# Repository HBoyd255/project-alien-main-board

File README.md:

# Project A.L.I.E.N. Main Board

<!-- Harry Boyd - hboyd255@gmail.com - 22/07/2024 -->

This is the repository for the main board of Project A.L.I.E.N. (Autonomous
Labyrinth Investigator, Explorer, Navigator).

This project started as a University project for the module
[Robotics Design and Construction](https://www.york.ac.uk/students/studying/manage/programmes/module-catalogue/module/ELE00098H).
To get us started, the University provided us with a main board, called the ARB
(Arduino Robotics Board), which was designed to break out the pins of an Arduino
Nano 33 BLE into connectors that were easier to use. However, when the module
concluded, the University wanted the boards back, so I designed my own.

## Testing

The code to test the board has been split into separate repositories.

- [Motors and Encoders](https://github.com/HBoyd255/project-alien-motor-test-code)
- [Bumper and NES Shift Registers](https://github.com/HBoyd255/project-alien-shift-register-test-code)
- [LED Strip and Level Shifter](https://github.com/HBoyd255/project-alien-led-strip-test-code)
- [Ultrasonic Sensor](https://github.com/HBoyd255/project-alien-ultrasonic-test-code)
- [Infrared Sensors and I2C Multiplexer](https://github.com/HBoyd255/project-alien-infrared-test-code)

## Expansion Boards

The Project A.L.I.E.N. Main Board has been designed to to take expansion boards.
This utilises the 3 left-over GPIO pins, D11, D12 and D13.

- [Extra buttons ](https://github.com/HBoyd255/project-alien-expansion-demo-buttons)

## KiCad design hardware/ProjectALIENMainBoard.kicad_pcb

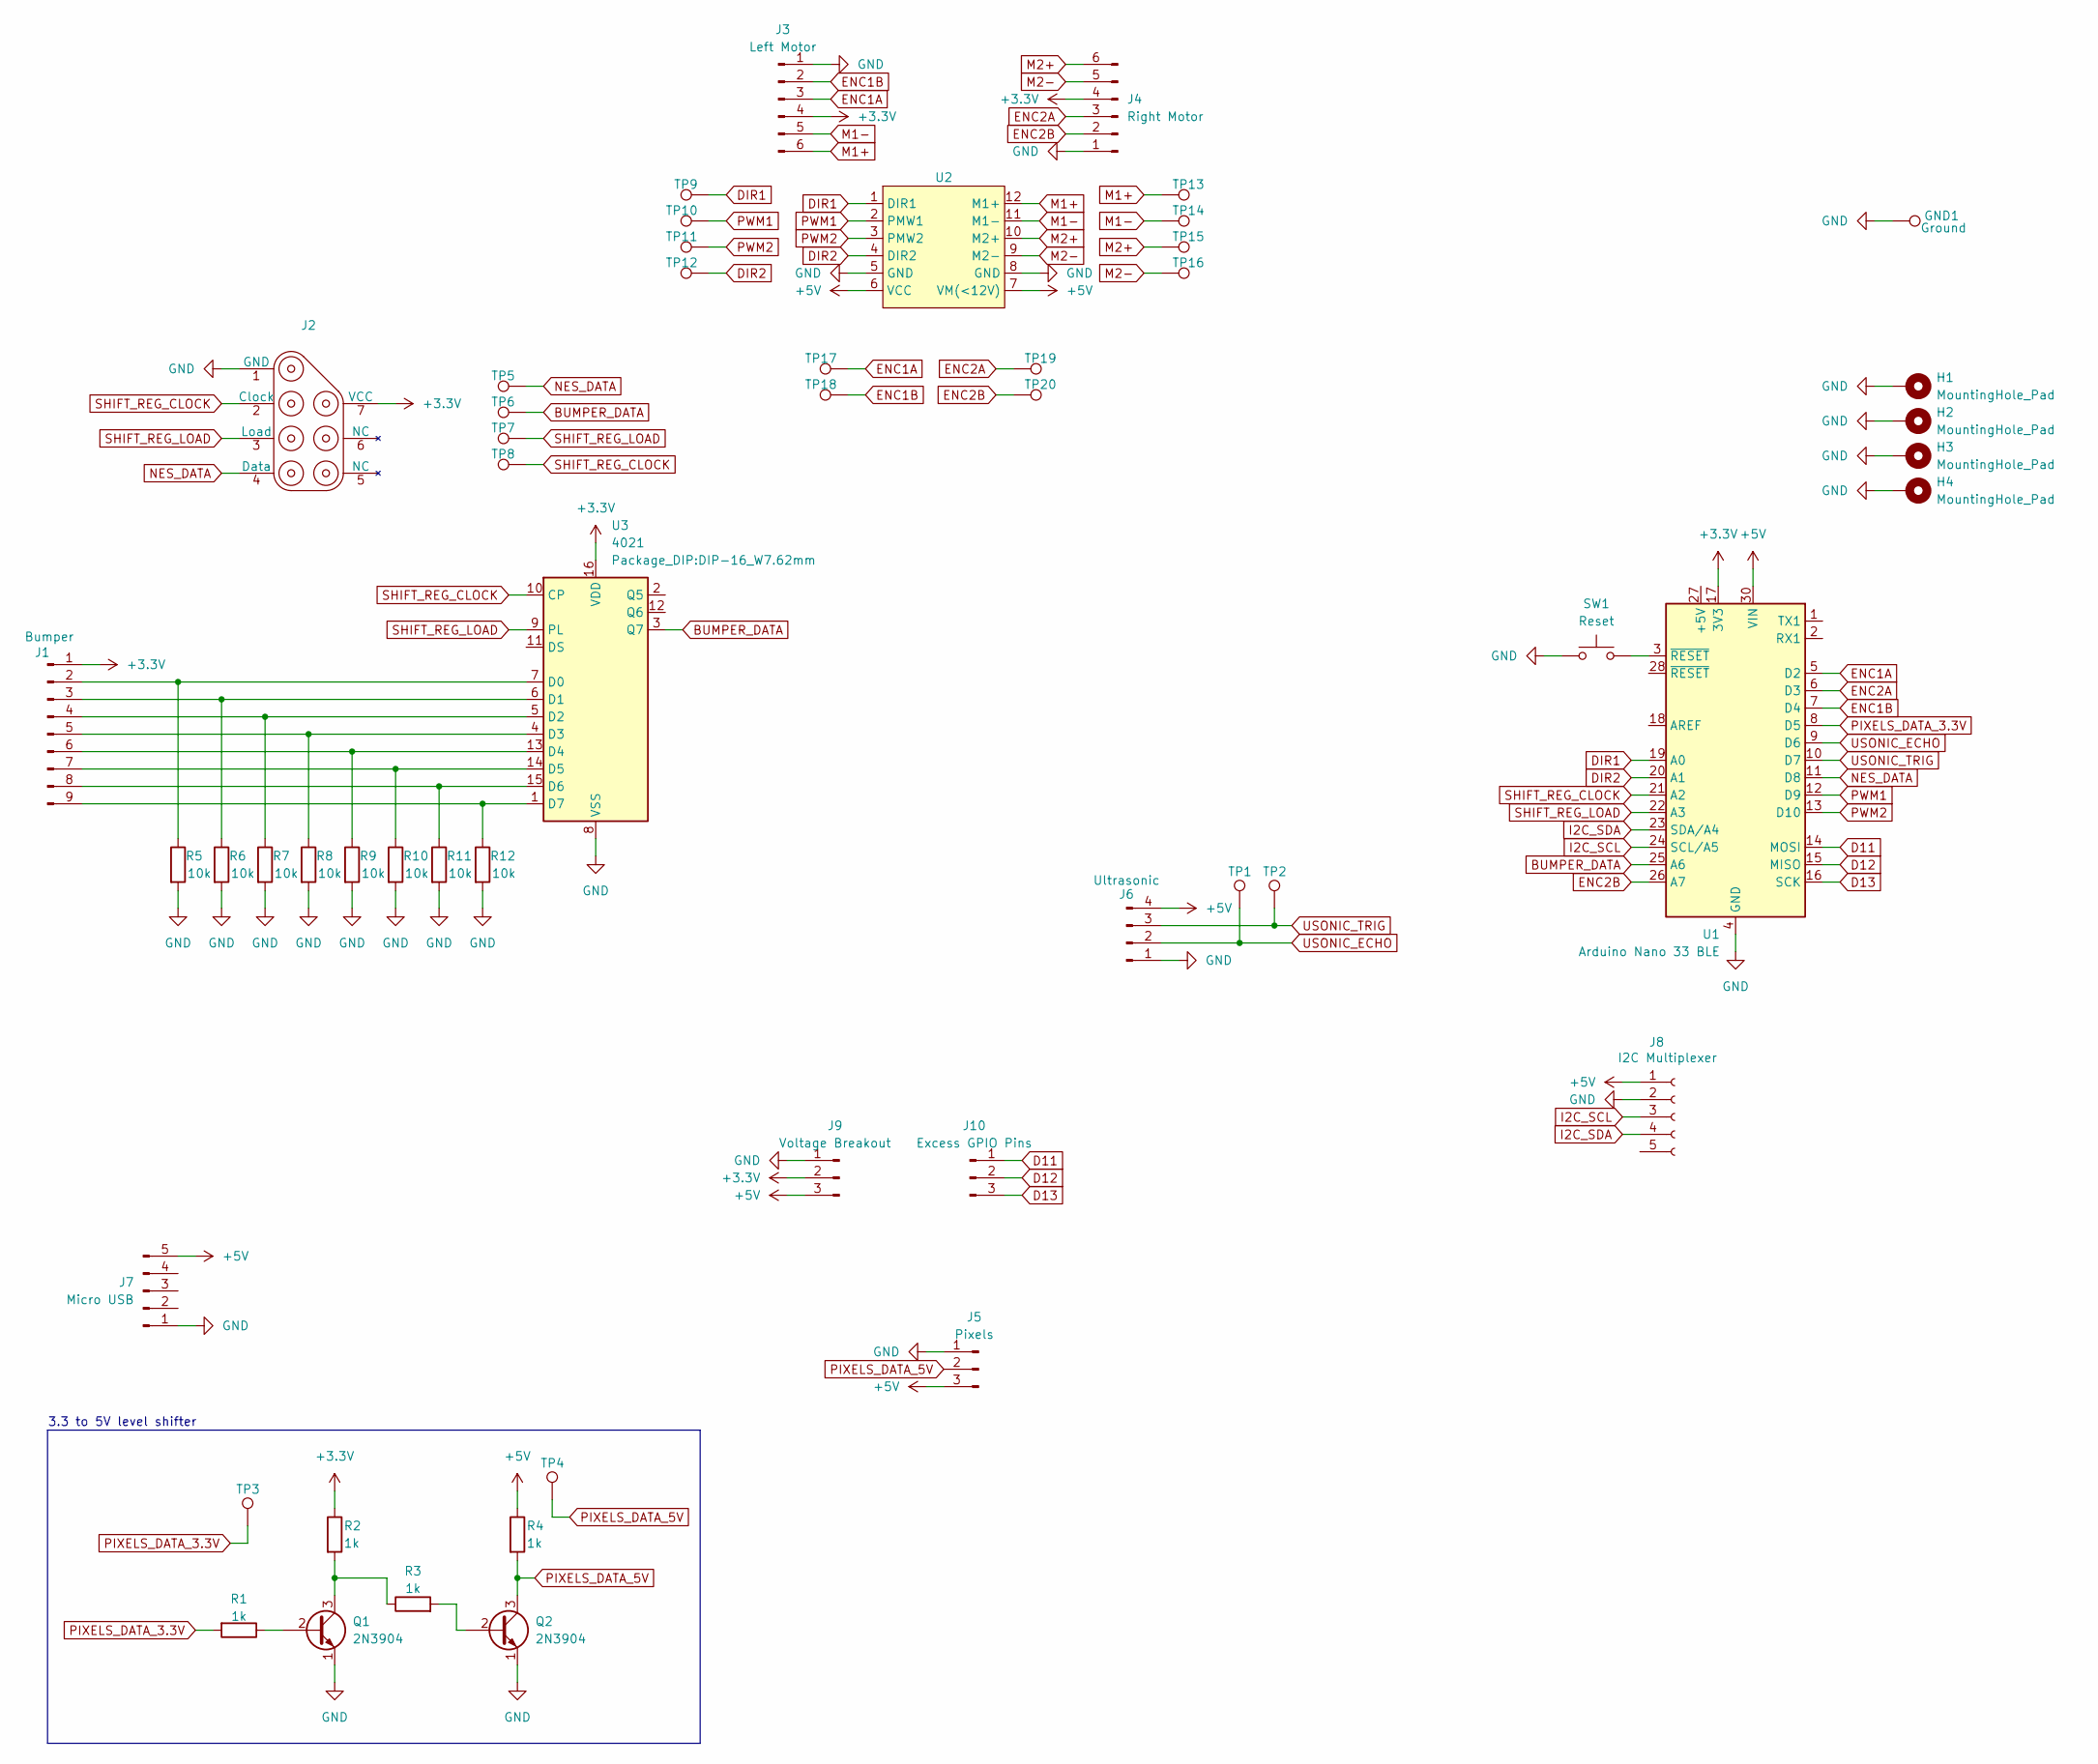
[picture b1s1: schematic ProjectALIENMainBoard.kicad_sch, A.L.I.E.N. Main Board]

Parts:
GND1: Ground; TestPoint_Bridge_Pitch2.54mm_Drill0.7mm
H1, H2, H3, H4: MountingHole_Pad; MountingHole_2.7mm_M2.5_Pad
J1: Bumper; PinHeader_1x09_P2.54mm_Horizontal
J2: NES_Controller_Port
J3: Left Motor; PinHeader_1x06_P2.54mm_Horizontal
J4: Right Motor; PinHeader_1x06_P2.54mm_Horizontal
J5: Pixels; PinHeader_1x03_P2.54mm_Vertical
J6: Ultrasonic; PinHeader_1x04_P2.54mm_Horizontal
J7: Micro USB; Adafruit_1833_Shield
J8: I2C Multiplexer; Adafruit_5664_Shield
J9: Voltage Breakout; PinHeader_1x03_P2.54mm_Vertical
J10: Excess GPIO Pins; PinHeader_1x03_P2.54mm_Vertical
Q1, Q2: 2N3904; TO-92_Inline
R1, R2, R3, R4: 1k; R_0402_1005Metric_Pad0.72x0.64mm_HandSolder
R5, R6, R7, R8, R9, R10, R11, R12: 10k; R_0402_1005Metric_Pad0.72x0.64mm_HandSolder
SW1: Reset; Two_Pin_Through_Hole_Push_Button
TP1, TP2, TP3, TP4, TP5, TP6, TP7, TP8, TP9, TP10, TP11, TP12, TP13, TP14, TP15, TP16, TP17, TP18, TP19, TP20: TestPoint; TestPoint_THTPad_D1.0mm_Drill0.5mm
U1: Arduino Nano 33 BLE; Arduino_Nano
U2: DFRobot_DC_Motor_Driver_Shield
U3: 4021; DIP-16_W7.62mm

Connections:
+3.3V: J1.1, J2.7 (VCC), J3.4, J4.4, J9.2, R2.1, U1.17 (3V3), U3.16 (VDD)
+5V: J5.3, J6.4, J7.5, J8.1, J9.3, R4.1, U1.30 (VIN), U2.6 (VCC), U2.7 (VM(<12V))
BUMPER_DATA: TP6.1, U1.25 (A6), U3.3 (Q7)
D11: J10.1, U1.14 (MOSI)
D12: J10.2, U1.15 (MISO)
D13: J10.3, U1.16 (SCK)
DIR1: TP9.1, U1.19 (A0), U2.1 (DIR1)
DIR2: TP12.1, U1.20 (A1), U2.4 (DIR2)
ENC1A: J3.3, TP17.1, U1.5 (D2)
ENC1B: J3.2, TP18.1, U1.7 (D4)
ENC2A: J4.3, TP19.1, U1.6 (D3)
ENC2B: J4.2, TP20.1, U1.26 (A7)
GND: GND1.1, H1.1, H2.1, H3.1, H4.1, J2.1 (GND), J3.1, J4.1, J5.1, J6.1, J7.1, J8.2, J9.1, Q1.1 (E), Q2.1 (E), R5.2, R6.2, R7.2, R8.2, R9.2, R10.2, R11.2, R12.2, SW1.1, U1.4 (GND), U1.29 (GND), U2.5 (GND), U2.8 (GND), U3.8 (VSS)
I2C_SCL: J8.3, U1.24 (SCL/A5)
I2C_SDA: J8.4, U1.23 (SDA/A4)
M1+: J3.6, TP13.1, U2.12 (M1+)
M1-: J3.5, TP14.1, U2.11 (M1-)
M2+: J4.6, TP15.1, U2.10 (M2+)
M2-: J4.5, TP16.1, U2.9 (M2-)
NES_DATA: J2.4 (Data), TP5.1, U1.11 (D8)
unnamed: J1.2, R5.1, U3.7 (D0)
unnamed: J1.3, R6.1, U3.6 (D1)
unnamed: J1.4, R7.1, U3.5 (D2)
unnamed: J1.5, R8.1, U3.4 (D3)
unnamed: J1.6, R9.1, U3.13 (D4)
unnamed: J1.7, R10.1, U3.14 (D5)
unnamed: J1.8, R11.1, U3.15 (D6)
unnamed: J1.9, R12.1, U3.1 (D7)
unnamed: Q1.2 (B), R1.1
unnamed: Q1.3 (C), R2.2, R3.1
unnamed: Q2.2 (B), R3.2
unnamed: SW1.2, U1.3 (~RESET)
PIXELS_DATA_3.3V: R1.2, TP3.1, U1.8 (D5)
PIXELS_DATA_5V: J5.2, Q2.3 (C), R4.2, TP4.1
PWM1: TP10.1, U1.12 (D9), U2.2 (PMW1)
PWM2: TP11.1, U1.13 (D10), U2.3 (PMW2)
SHIFT_REG_CLOCK: J2.2 (Clock), TP8.1, U1.21 (A2), U3.10 (CP)
SHIFT_REG_LOAD: J2.3 (Load), TP7.1, U1.22 (A3), U3.9 (PL)
USONIC_ECHO: J6.2, TP1.1, U1.9 (D6)
USONIC_TRIG: J6.3, TP2.1, U1.10 (D7)

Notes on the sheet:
3.3 to 5V level shifter

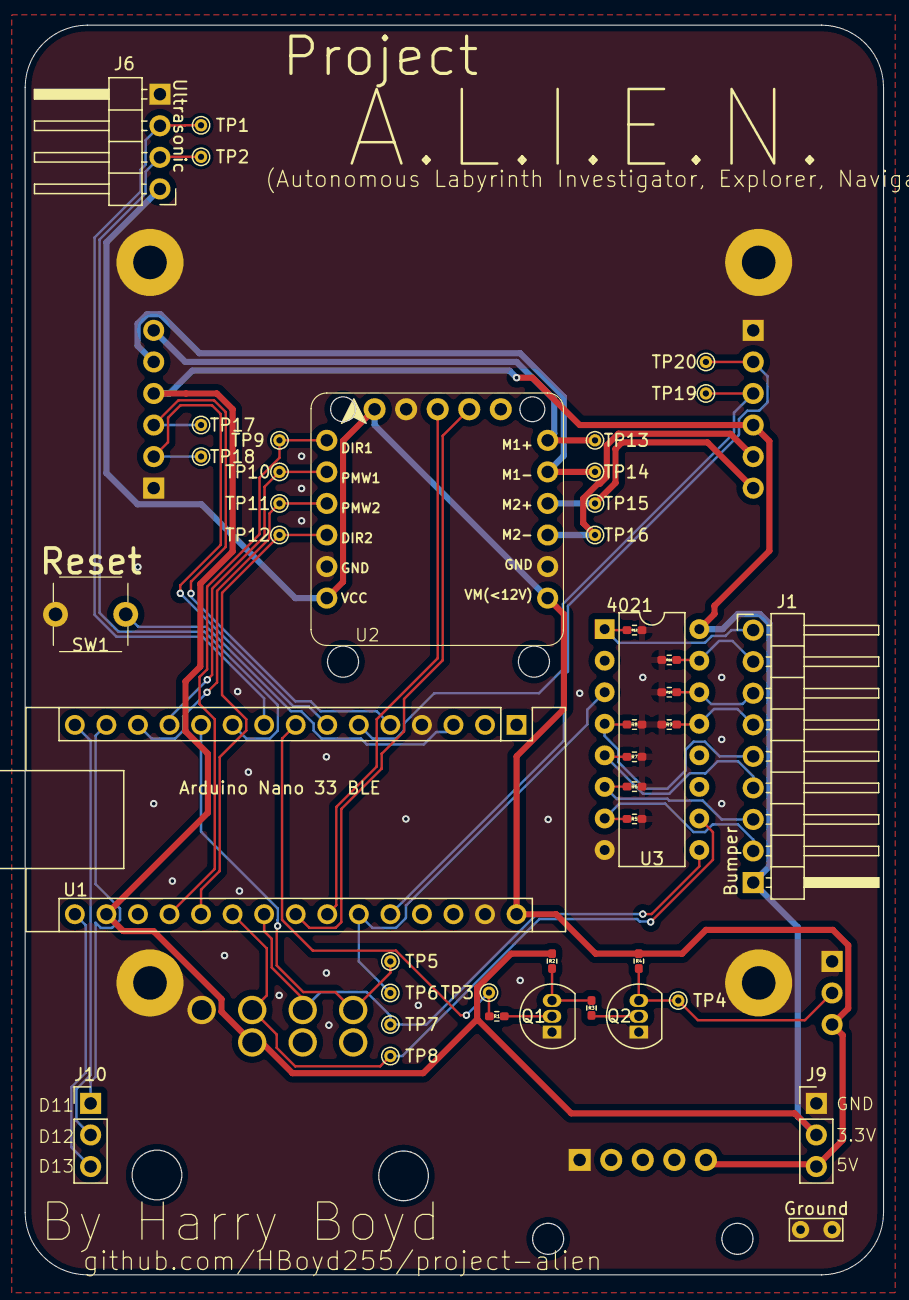
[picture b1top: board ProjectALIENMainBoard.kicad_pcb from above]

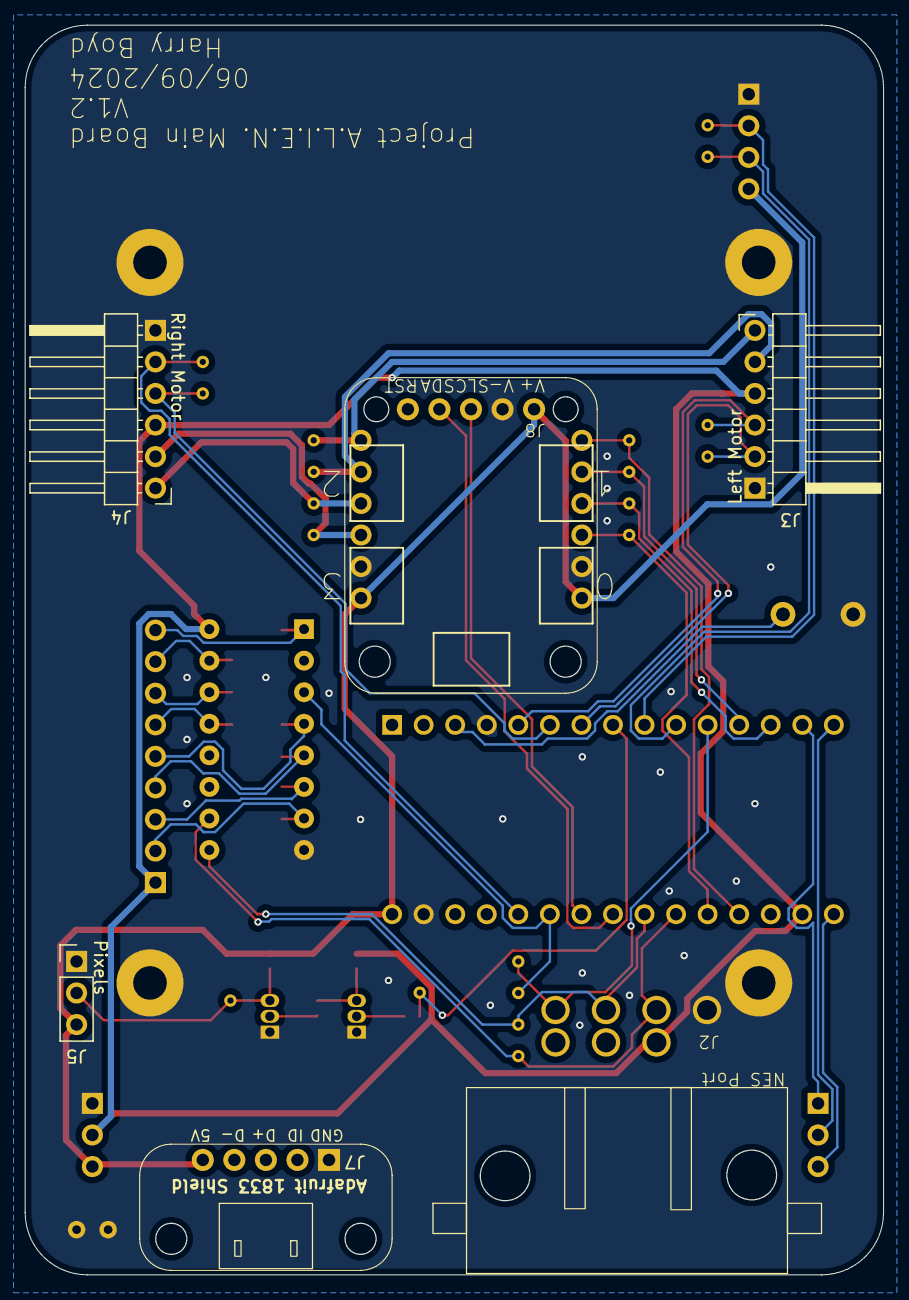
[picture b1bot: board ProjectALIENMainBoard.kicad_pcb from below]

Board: 2 copper layers, 69.1 x 100.5 mm, 53 parts (6 on the bottom side), 40 nets.

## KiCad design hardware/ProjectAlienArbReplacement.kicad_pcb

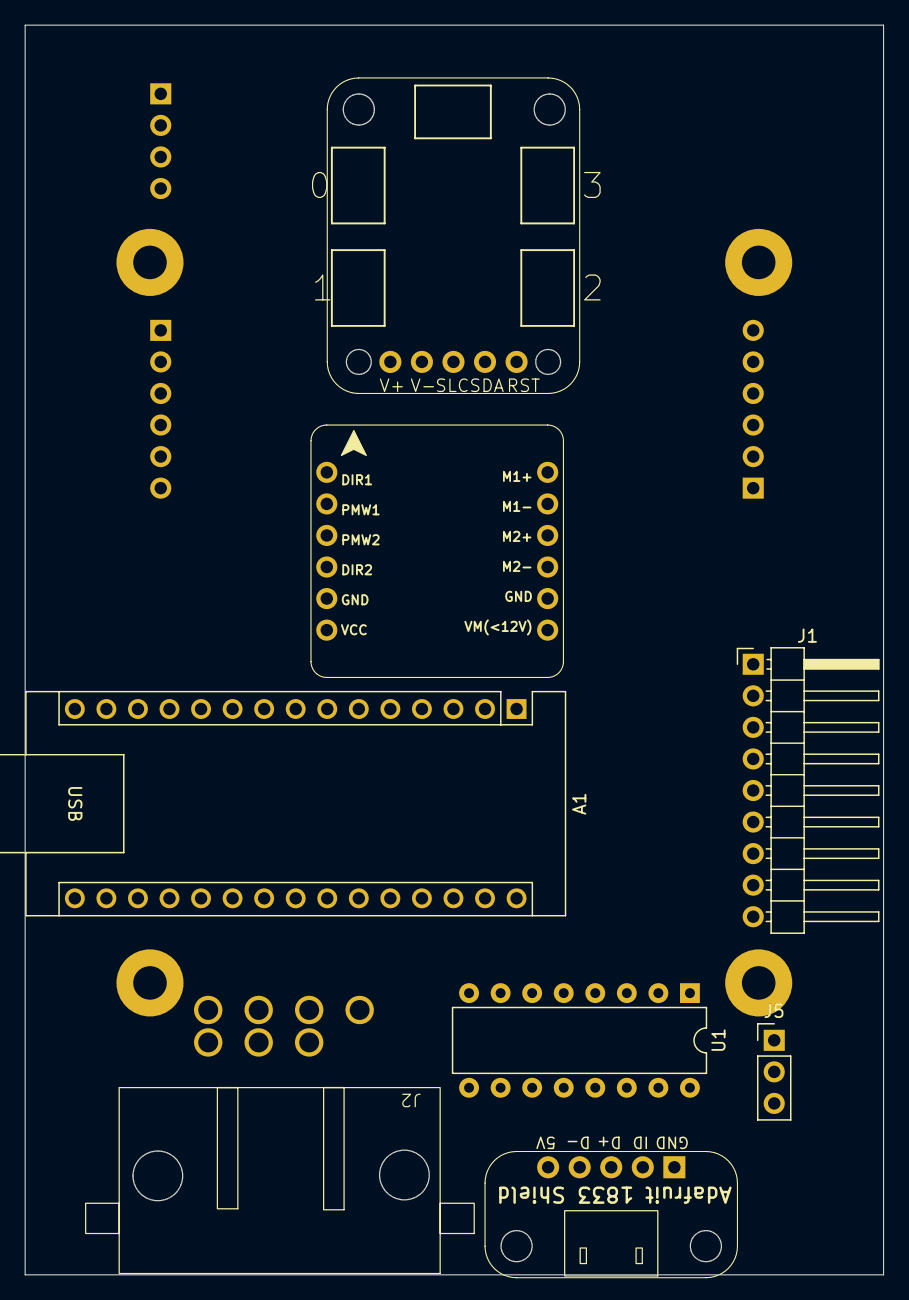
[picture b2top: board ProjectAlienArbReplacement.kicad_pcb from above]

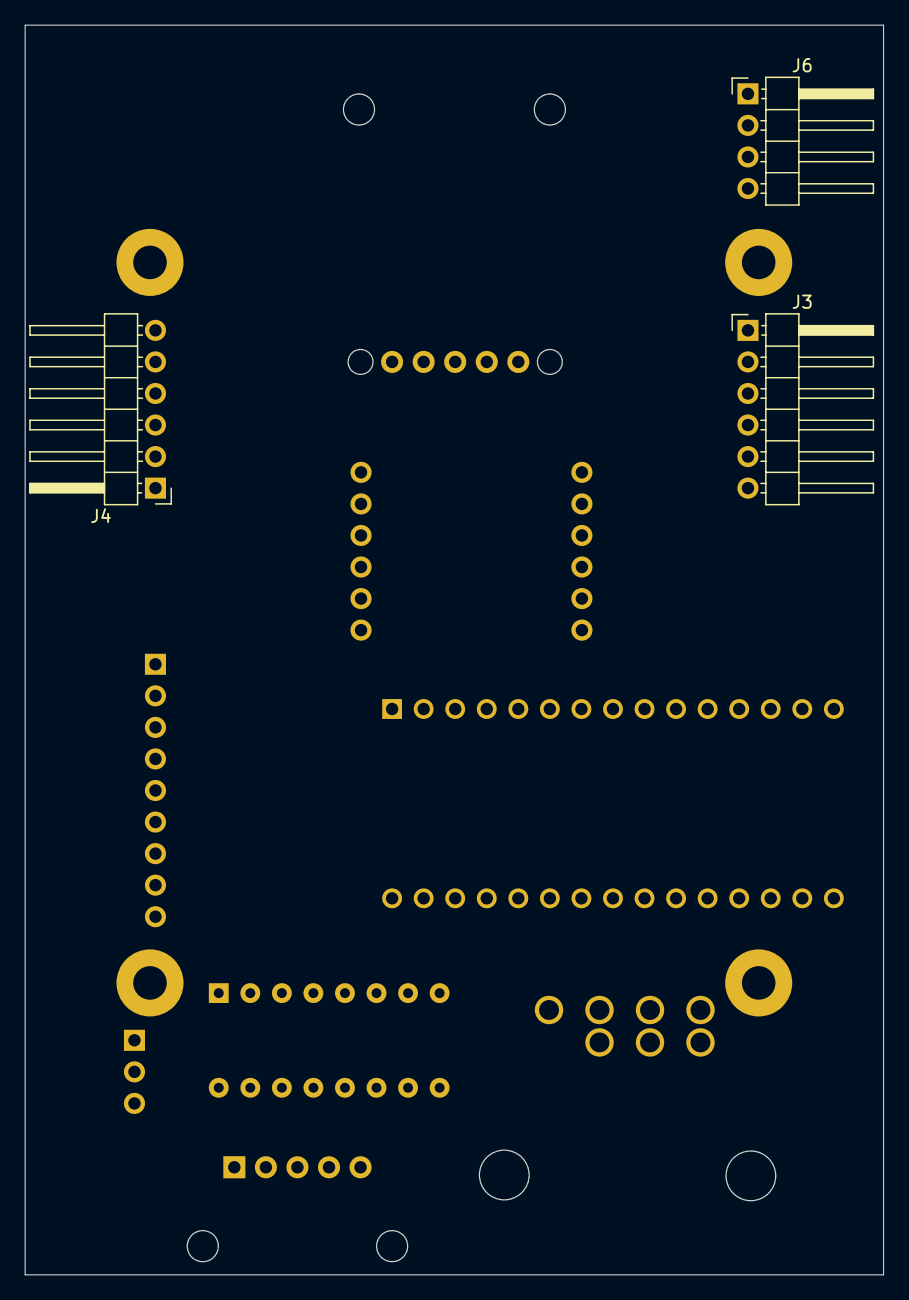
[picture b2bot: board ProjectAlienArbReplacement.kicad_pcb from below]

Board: 2 copper layers, 69.1 x 100.5 mm, 15 parts (3 on the bottom side), 19 nets, no tracks yet.

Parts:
A1: Arduino_Nano_Every; Arduino_Nano
H1, H2, H3, H4: MountingHole_Pad; MountingHole_2.7mm_M2.5_Pad
J1: Bumper Connector; PinHeader_1x09_P2.54mm_Horizontal
J2: NES_Controller_Port
J3: Left Motor Connector; PinHeader_1x06_P2.54mm_Horizontal
J4: Right Motor Connector; PinHeader_1x06_P2.54mm_Horizontal
J5: Pixels Connector; PinHeader_1x03_P2.54mm_Vertical
J6: Ultrasonic Connector; PinHeader_1x04_P2.54mm_Horizontal
J7: Micro USB; Adafruit_1833_Shield
J8: I2C Multiplexer; Adafruit_5664_Shield
M1: DFRobot_DC_Motor_Driver_Shield
U1: 4021; DIP-16_W7.62mm

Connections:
+5V: J1.1, J2.7 (VCC), U1.16 (VDD)
BUMPER_DATA: A1.25 (A6), U1.11 (DS)
GND: H1.1, H2.1, H3.1, H4.1, J2.1 (GND), M1.5 (GND), M1.8 (GND), U1.8 (VSS)
NES_DATA: A1.11 (D8), J2.4 (Data)
unnamed: A1.19 (A0), M1.1 (DIR1)
unnamed: A1.20 (A1), M1.4 (DIR2)
unnamed: A1.12 (D9), M1.2 (PMW1)
unnamed: A1.13 (D10), M1.3 (PMW2)
unnamed: A1.4 (GND), A1.29 (GND)
unnamed: J1.2, U1.7 (D0)
unnamed: J1.3, U1.6 (D1)
unnamed: J1.4, U1.5 (D2)
unnamed: J1.5, U1.4 (D3)
unnamed: J1.6, U1.13 (D4)
unnamed: J1.7, U1.14 (D5)
unnamed: J1.8, U1.15 (D6)
unnamed: J1.9, U1.1 (D7)
SHIFT_REG_CLOCK: A1.21 (A2), J2.2 (Clock), U1.10 (CP)
SHIFT_REG_LOAD: A1.22 (A3), J2.3 (Load), U1.9 (PL)

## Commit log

2024-07-22 Created repo
2024-07-22 Created empty kicad project
2024-07-23 Placed first draft of connectors
2024-07-28 Added I2C multiplexer
2024-07-28 Added motor driver
2024-07-28 Fixed screw hole size
2024-07-28 Updated pcb boarder
2024-07-28 Plated mount holes
2024-08-13 Added systemInfo.h
2024-08-13 Added test code to README.md
2024-08-13 Updated name to Project A.L.I.E.N. Main Board
2024-08-13 Updated name in README.md
2024-08-13 Swapped resistors for SMT
2024-08-14 Routed Tracks
2024-08-14 Added ground plane
2024-08-14 Fixed all errors
2024-08-14 Finished component silkscreen labels
2024-08-14 Updated text
2024-08-14 Added title to PCB
2024-08-15 Increased size of name
2024-08-15 Tweaked silkscreen
2024-08-15 Generated gerber version 1
2024-08-16 Capitalised ALIEN
2024-08-16 Changing name capitalisation
2024-08-16 Changed name capitalisation
2024-08-23 Added Expansion Boards to README.md
2024-08-23 Added board into to silkscreen (V1.0)
2024-08-23 Started listing issues with V1.0
2024-08-23 Added labels to Pixels connector
2024-08-23 Tidied up traces
2024-08-24 Fixed direction of connectors
2024-08-24 Fixed connector Issues
2024-08-24 Updated designators
2024-08-24 Updated labels for pixels
2024-08-24 Moved pixels labels again
2024-08-24 Generated gerber files (V1.1)
2024-08-24 Removed V1.0Issues.md
2024-09-06 Flipped and repositioned motor connectors
2024-09-06 Generated v1.2 gerber
